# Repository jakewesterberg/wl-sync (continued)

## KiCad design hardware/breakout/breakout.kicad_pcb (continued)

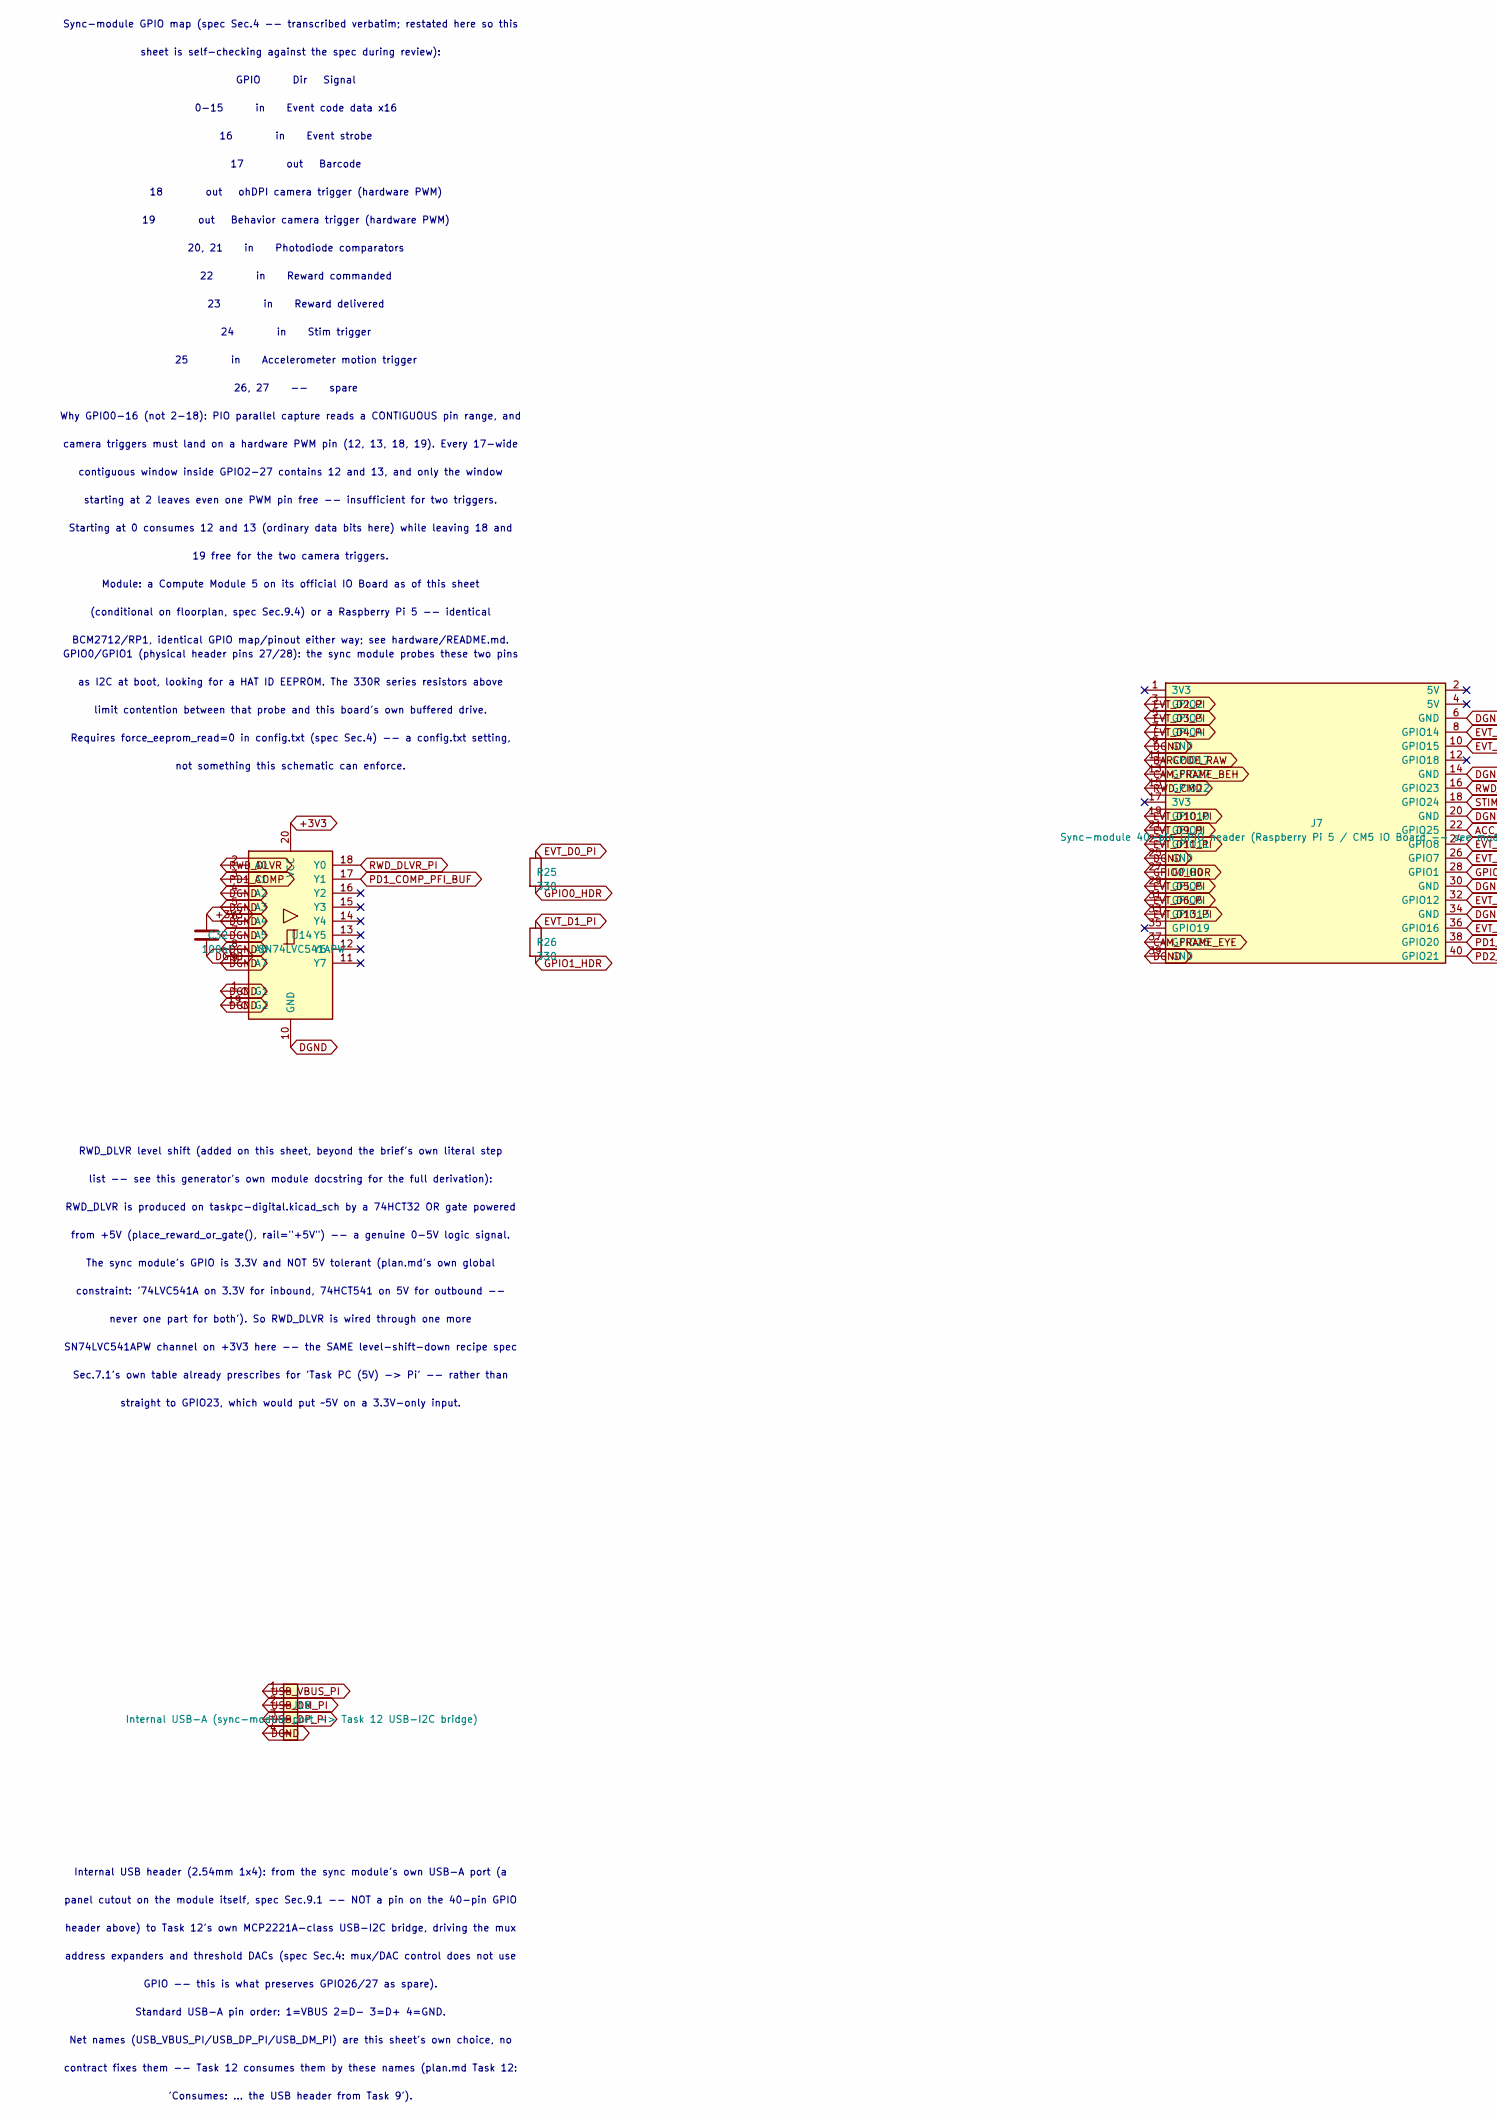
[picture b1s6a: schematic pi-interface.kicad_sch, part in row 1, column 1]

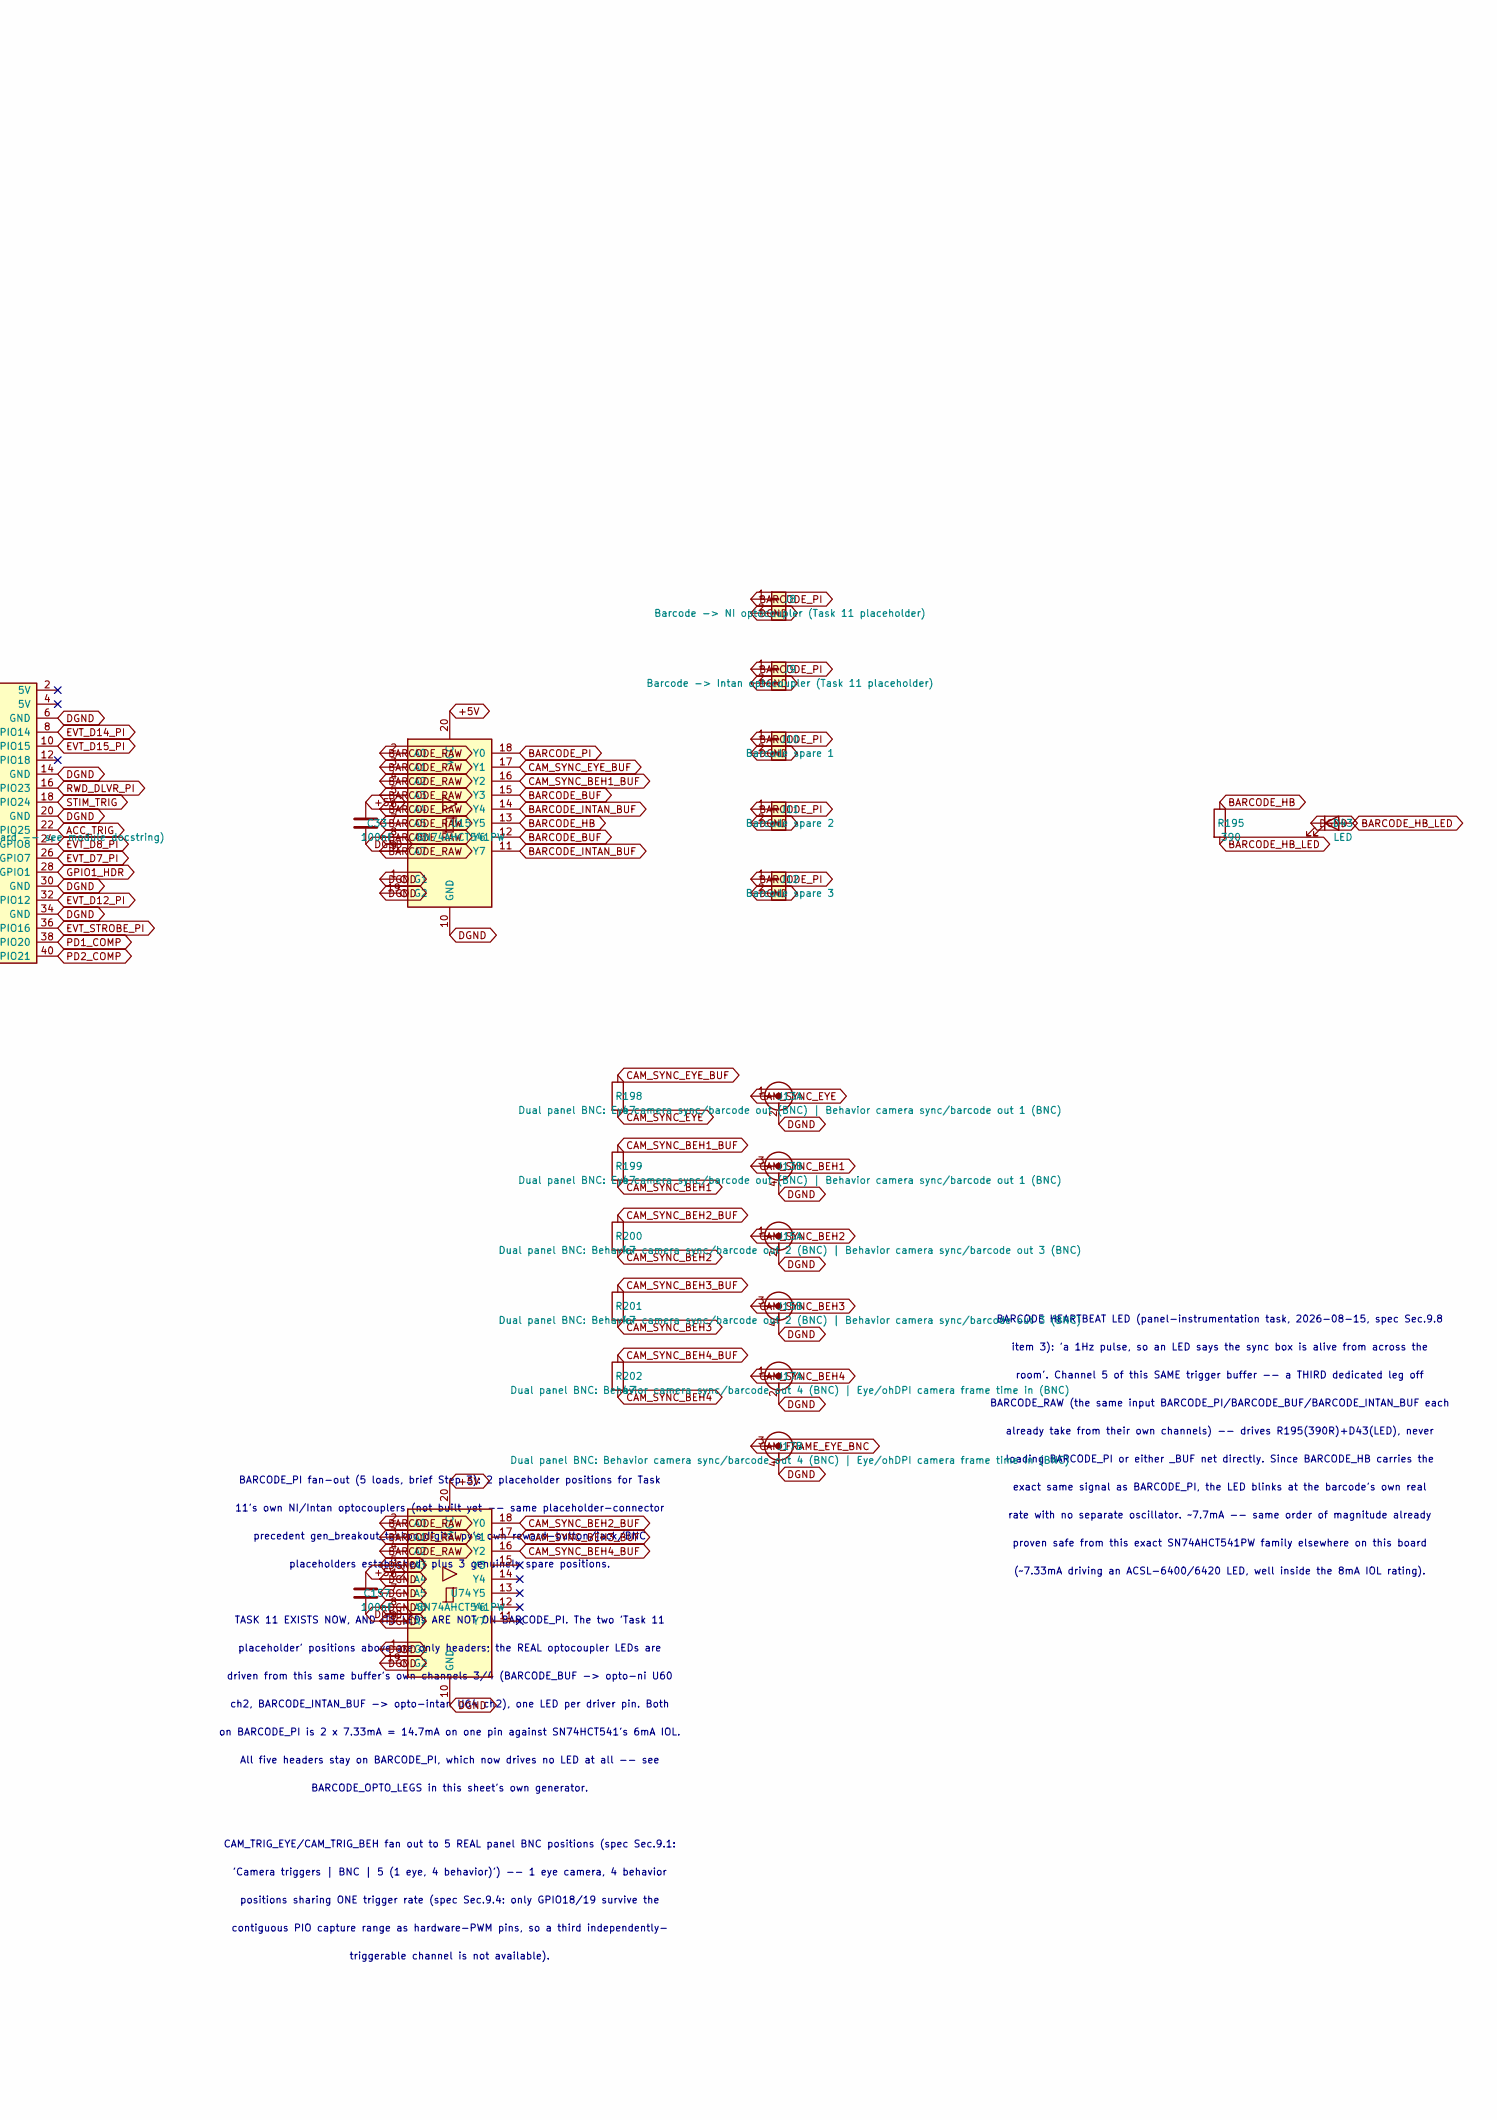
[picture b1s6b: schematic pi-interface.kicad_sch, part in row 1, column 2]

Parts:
C32, C33, C157: 100nF; C_0603_1608Metric
D43: LED; LED_0603_1608Metric_Pad1.05x0.95mm_HandSolder
J7: Sync-module 40-pin GPIO header (Raspberry Pi 5 / 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; PinHeader_2x20_P2.54mm_Vertical
J8: Barcode -> NI optocoupler (Task 11 placeholder); PinHeader_1x02_P2.54mm_Vertical
J9: Barcode -> Intan optocoupler (Task 11 placeholder); PinHeader_1x02_P2.54mm_Vertical
J10: Barcode spare 1; PinHeader_1x02_P2.54mm_Vertical
J11: Barcode spare 2; PinHeader_1x02_P2.54mm_Vertical
J12: Barcode spare 3; PinHeader_1x02_P2.54mm_Vertical
J13: Dual panel BNC: Eye camera sync/barcode out (BNC)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; BNC_Dual_RA_Isolated
J15, J17: Dual panel BNC: Behavior camera sync/barcode out 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; BNC_Dual_RA_Isolated
J18: Internal USB-A (sync-module port -> Task 12 USB-I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; PinHeader_1x04_P2.54mm_Vertical
R25, R26: 330; R_0603_1608Metric
R195: 390; R_0603_1608Metric
R198, R199, R200, R201, R202: 47; R_0603_1608Metric
U14: SN74LVC541APW; Texas_PW0020A_TSSOP-20_4.4x6.5mm_P0.65mm
U15, U74: SN74AHCT541PW; Texas_PW0020A_TSSOP-20_4.4x6.5mm_P0.65mm

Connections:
+3V3: C32.1, U14.20 (VCC); also elsewhere on the board
ACC_TRIG: J7.22 (GPIO25); also elsewhere on the board
BARCODE_BUF: U15.12 (Y6), U15.15 (Y3); also elsewhere on the board
BARCODE_HB: R195.1, U15.13 (Y5)
BARCODE_HB_LED: D43.2 (A), R195.2
BARCODE_INTAN_BUF: U15.11 (Y7), U15.14 (Y4); also elsewhere on the board
BARCODE_PI: J8.1, J9.1, J10.1, J11.1, J12.1, U15.18 (Y0)
BARCODE_RAW: J7.11 (GPIO17), U15.2 (A0), U15.3 (A1), U15.4 (A2), U15.5 (A3), U15.6 (A4), U15.7 (A5), U15.8 (A6), U15.9 (A7), U74.2 (A0), U74.3 (A1), U74.4 (A2)
CAM_FRAME_BEH: J7.13 (GPIO27); also elsewhere on the board
CAM_FRAME_EYE: J7.37 (GPIO26); also elsewhere on the board
CAM_FRAME_EYE_BNC: J17.3 (B_In); also elsewhere on the board
CAM_SYNC_BEH1: J13.3 (B_In), R199.2
CAM_SYNC_BEH1_BUF: R199.1, U15.16 (Y2)
CAM_SYNC_BEH2: J15.1 (A_In), R200.2
CAM_SYNC_BEH2_BUF: R200.1, U74.18 (Y0)
CAM_SYNC_BEH3: J15.3 (B_In), R201.2
CAM_SYNC_BEH3_BUF: R201.1, U74.17 (Y1)
CAM_SYNC_BEH4: J17.1 (A_In), R202.2
CAM_SYNC_BEH4_BUF: R202.1, U74.16 (Y2)
CAM_SYNC_EYE: J13.1 (A_In), R198.2
CAM_SYNC_EYE_BUF: R198.1, U15.17 (Y1)
EVT_D0_PI: R25.1; also elsewhere on the board
EVT_D1_PI: R26.1; also elsewhere on the board
EVT_D2_PI: J7.3 (GPIO2); also elsewhere on the board
EVT_D3_PI: J7.5 (GPIO3); also elsewhere on the board
EVT_D4_PI: J7.7 (GPIO4); also elsewhere on the board
EVT_D5_PI: J7.29 (GPIO5); also elsewhere on the board
EVT_D6_PI: J7.31 (GPIO6); also elsewhere on the board
EVT_D7_PI: J7.26 (GPIO7); also elsewhere on the board
EVT_D8_PI: J7.24 (GPIO8); also elsewhere on the board
EVT_D9_PI: J7.21 (GPIO9); also elsewhere on the board
EVT_D10_PI: J7.19 (GPIO10); also elsewhere on the board
EVT_D11_PI: J7.23 (GPIO11); also elsewhere on the board
EVT_D12_PI: J7.32 (GPIO12); also elsewhere on the board
EVT_D13_PI: J7.33 (GPIO13); also elsewhere on the board
EVT_D14_PI: J7.8 (GPIO14); also elsewhere on the board
EVT_D15_PI: J7.10 (GPIO15); also elsewhere on the board
EVT_STROBE_PI: J7.36 (GPIO16); also elsewhere on the board
GPIO0_HDR: J7.27 (GPIO0), R25.2
GPIO1_HDR: J7.28 (GPIO1), R26.2
PD1_COMP: J7.38 (GPIO20), U14.3 (A1); also elsewhere on the board
PD1_COMP_PFI_BUF: U14.17 (Y1); also elsewhere on the board
PD2_COMP: J7.40 (GPIO21); also elsewhere on the board
RWD_CMD: J7.15 (GPIO22); also elsewhere on the board
RWD_DLVR: U14.2 (A0); also elsewhere on the board
RWD_DLVR_PI: J7.16 (GPIO23), U14.18 (Y0)
STIM_TRIG: J7.18 (GPIO24); also elsewhere on the board
USB_DM_PI: J18.2; also elsewhere on the board
USB_DP_PI: J18.3; also elsewhere on the board
USB_VBUS_PI: J18.1

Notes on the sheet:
not something this schematic can enforce.
Sec.7.1's own table already prescribes for 'Task PC (5V) -> Pi' -- rather than
as I2C at boot, looking for a HAT ID EEPROM. The 330R series resistors above
constraint: '74LVC541A on 3.3V for inbound, 74HCT541 on 5V for outbound --
contiguous window inside GPIO2-27 contains 12 and 13, and only the window
24 in Stim trigger
Sync-module GPIO map (spec Sec.4 -- transcribed verbatim; restated here so this
RWD_DLVR is produced on taskpc-digital.kicad_sch by a 74HCT32 OR gate powered
GPIO0/GPIO1 (physical header pins 27/28): the sync module probes these two pins
ch2, BARCODE_INTAN_BUF -> opto-intan U64 ch2), one LED per driver pin. Both
(~7.33mA driving an ACSL-6400/6420 LED, well inside the 8mA IOL rating).
precedent gen_breakout_taskpc_digital.py's own reward-button/jack/BNC
0-15 in Event code data x16
already take from their own channels) -- drives R195(390R)+D43(LED), never
GPIO Dir Signal
BARCODE HEARTBEAT LED (panel-instrumentation task, 2026-08-15, spec Sec.9.8
SN74LVC541APW channel on +3V3 here -- the SAME level-shift-down recipe spec
exact same signal as BARCODE_PI, the LED blinks at the barcode's own real
camera triggers must land on a hardware PWM pin (12, 13, 18, 19). Every 17-wide
contiguous PIO capture range as hardware-PWM pins, so a third independently-
BCM2712/RP1, identical GPIO map/pinout either way; see hardware/README.md.
CAM_TRIG_EYE/CAM_TRIG_BEH fan out to 5 REAL panel BNC positions (spec Sec.9.1:
placeholders established) plus 3 genuinely spare positions.
Requires force_eeprom_read=0 in config.txt (spec Sec.4) -- a config.txt setting,
23 in Reward delivered
Why GPIO0-16 (not 2-18): PIO parallel capture reads a CONTIGUOUS pin range, and
address expanders and threshold DACs (spec Sec.4: mux/DAC control does not use
11's own NI/Intan optocouplers (not built yet -- same placeholder-connector
never one part for both'). So RWD_DLVR is wired through one more
Net names (USB_VBUS_PI/USB_DP_PI/USB_DM_PI) are this sheet's own choice, no
Standard USB-A pin order: 1=VBUS 2=D- 3=D+ 4=GND.
'Camera triggers | BNC | 5 (1 eye, 4 behavior)') -- 1 eye camera, 4 behavior
BARCODE_RAW (the same input BARCODE_PI/BARCODE_BUF/BARCODE_INTAN_BUF each
on BARCODE_PI is 2 x 7.33mA = 14.7mA on one pin against SN74HCT541's 6mA IOL.
room'. Channel 5 of this SAME trigger buffer -- a THIRD dedicated leg off
panel cutout on the module itself, spec Sec.9.1 -- NOT a pin on the 40-pin GPIO
BARCODE_OPTO_LEGS in this sheet's own generator.
triggerable channel is not available).
16 in Event strobe
18 out ohDPI camera trigger (hardware PWM)

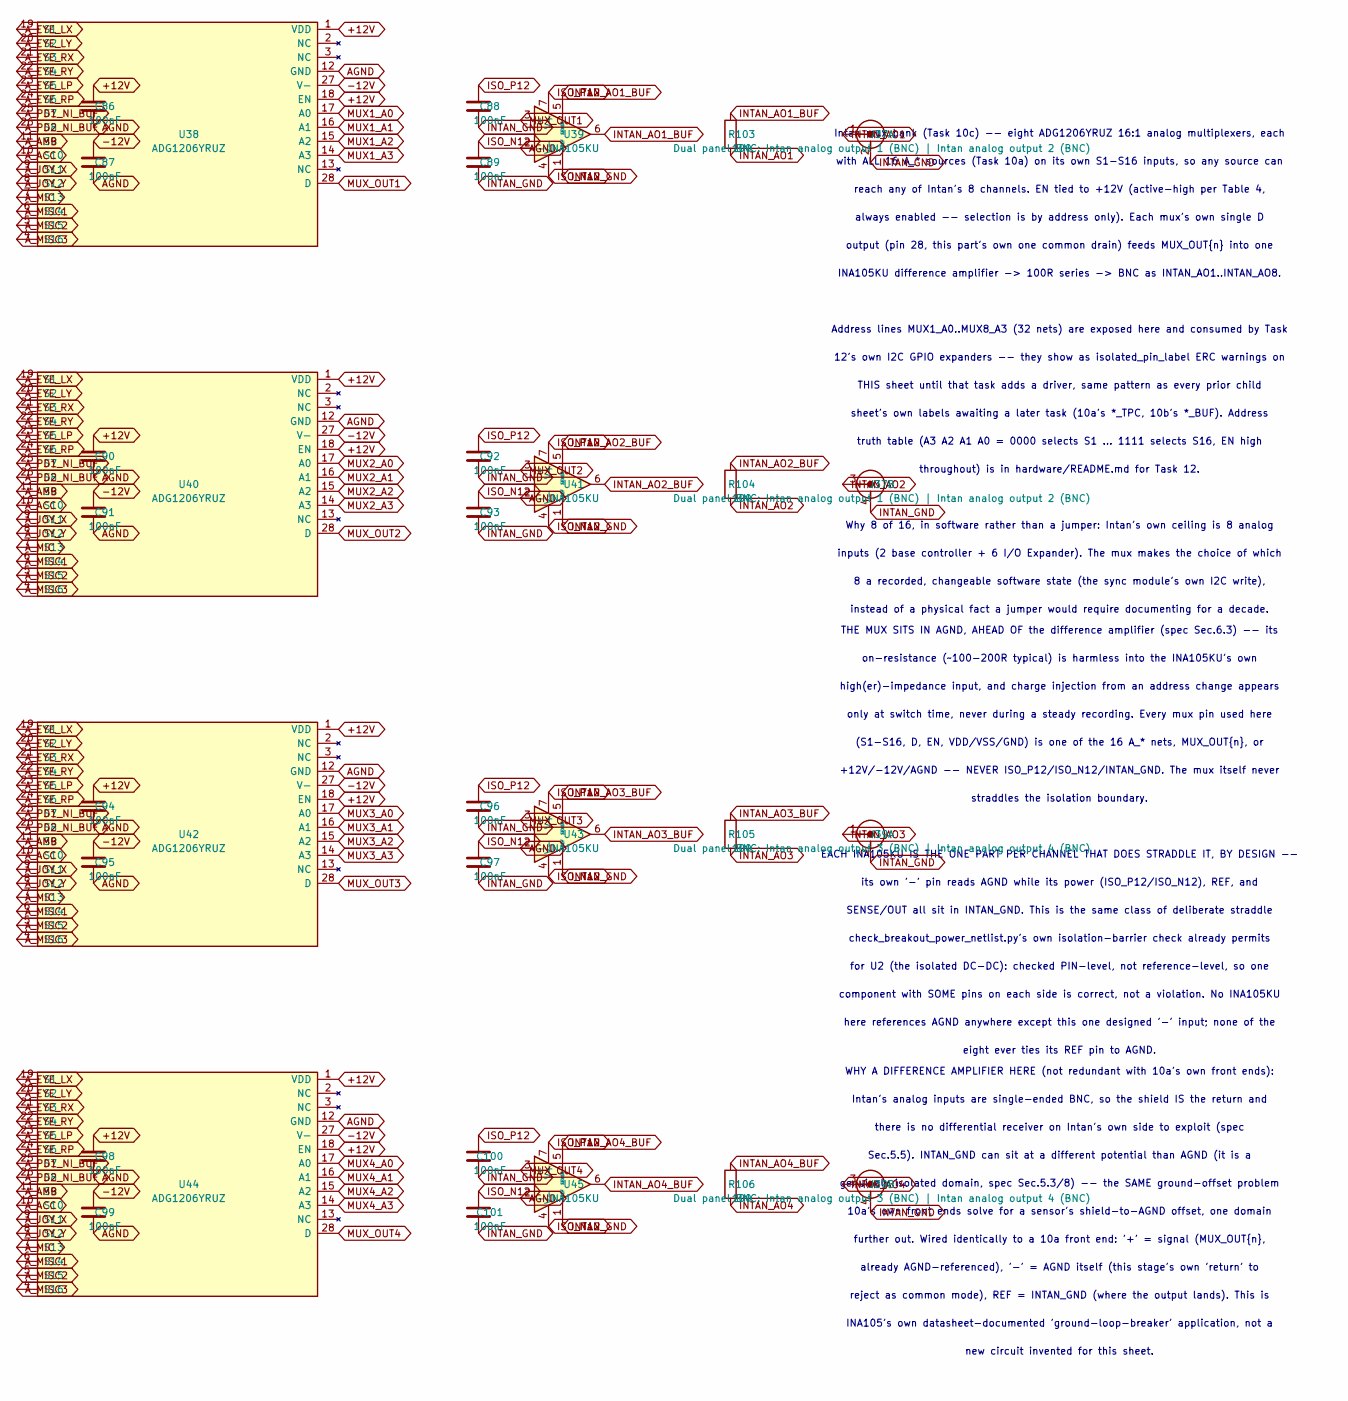
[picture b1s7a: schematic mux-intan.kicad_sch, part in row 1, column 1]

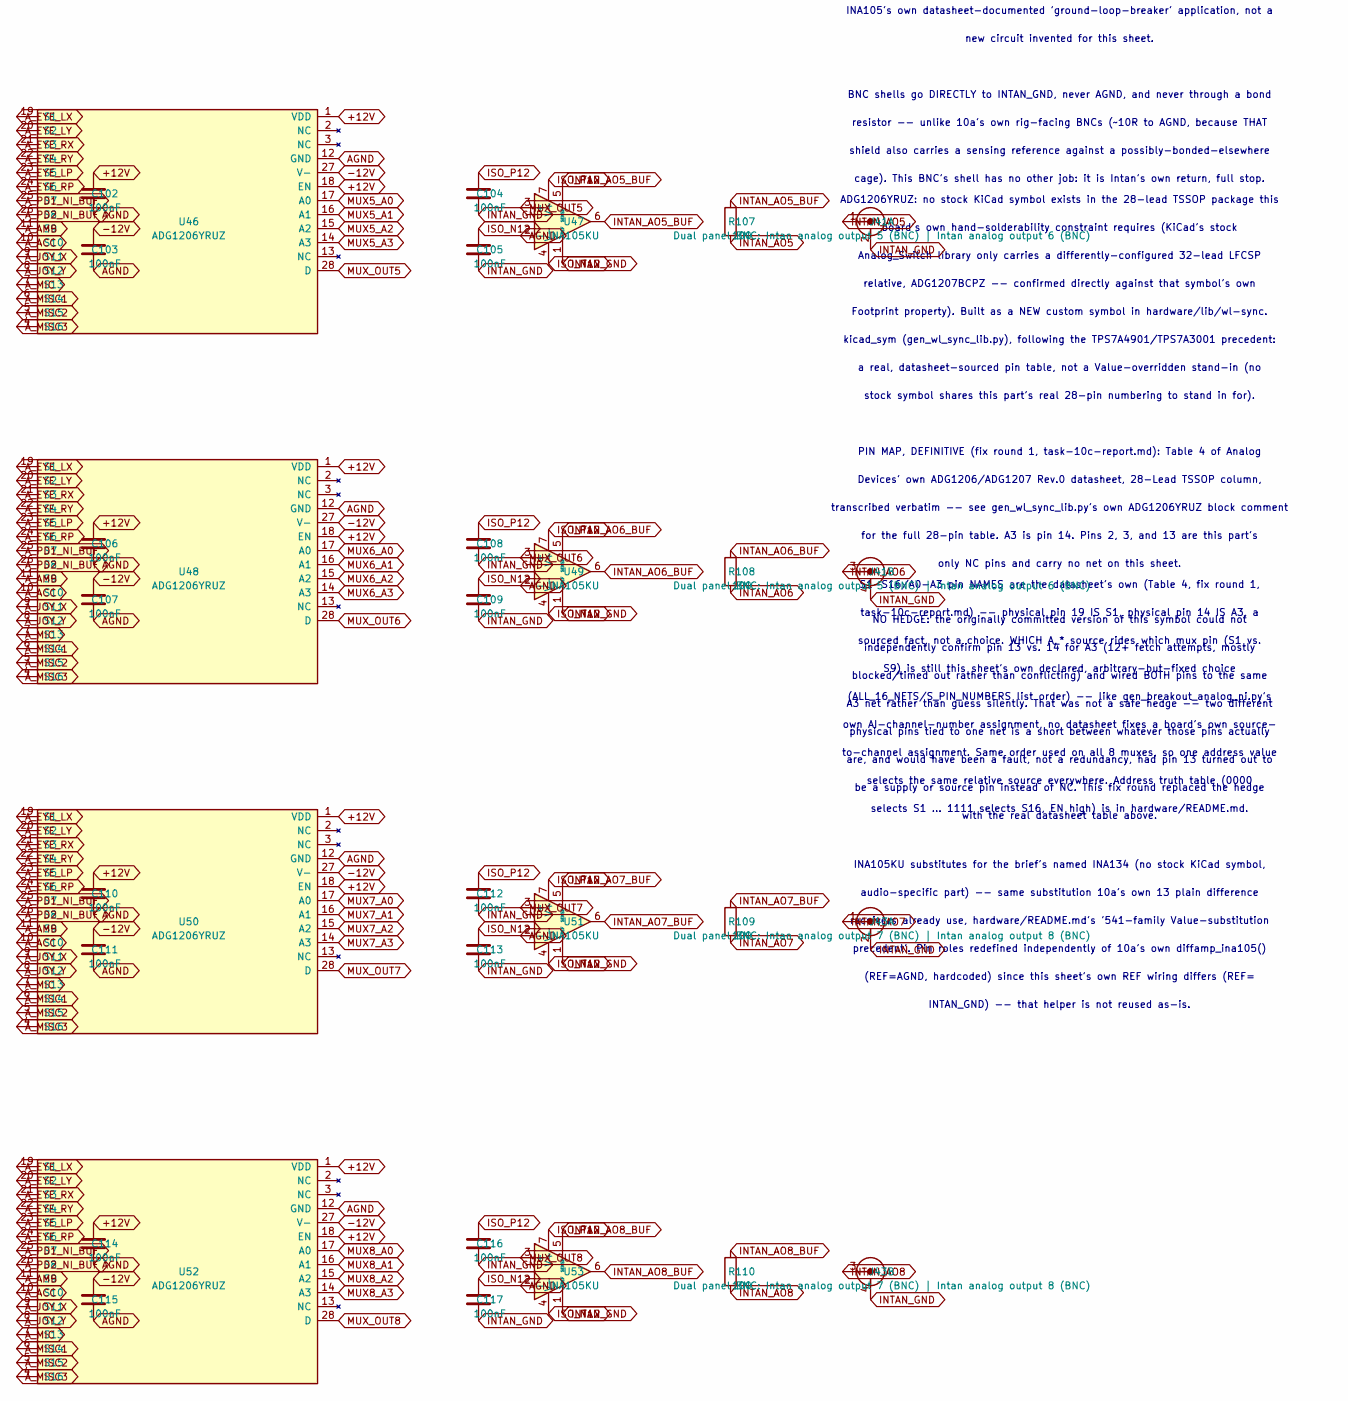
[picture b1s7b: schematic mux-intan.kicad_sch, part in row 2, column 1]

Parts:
C86, C87, C88, C89, C90, C91, C92, C93, C94, C95, C96, C97, C98, C99, C100, C101, C102, C103, C104, C105, C106, C107, C108, C109, C110, C111, C112, C113, C114, C115, C116, C117: 100nF; C_0603_1608Metric
J37: Dual panel BNC: Intan analog output 1 (BNC) | Int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; BNC_Dual_RA_Isolated
J39: Dual panel BNC: Intan analog output 3 (BNC) | Int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; BNC_Dual_RA_Isolated
J41: Dual panel BNC: Intan analog output 5 (BNC) | Int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; BNC_Dual_RA_Isolated
J43: Dual panel BNC: Intan analog output 7 (BNC) | Int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; BNC_Dual_RA_Isolated
R103, R104, R105, R106, R107, R108, R109, R110: 100; R_0603_1608Metric
U38, U40, U42, U44, U46, U48, U50, U52: ADG1206YRUZ; TSSOP-28_4.4x9.7mm_P0.65mm
U39, U41, U43, U45, U47, U49, U51, U53: INA105KU; SOIC-8_3.9x4.9mm_P1.27mm

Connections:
A_ACC: U38.10 (S10), U40.10 (S10), U42.10 (S10), U44.10 (S10), U46.10 (S10), U48.10 (S10), U50.10 (S10), U52.10 (S10); also elsewhere on the board
A_AMB: U38.11 (S9), U40.11 (S9), U42.11 (S9), U44.11 (S9), U46.11 (S9), U48.11 (S9), U50.11 (S9), U52.11 (S9); also elsewhere on the board
A_EYE_LP: U38.23 (S5), U40.23 (S5), U42.23 (S5), U44.23 (S5), U46.23 (S5), U48.23 (S5), U50.23 (S5), U52.23 (S5); also elsewhere on the board
A_EYE_LX: U38.19 (S1), U40.19 (S1), U42.19 (S1), U44.19 (S1), U46.19 (S1), U48.19 (S1), U50.19 (S1), U52.19 (S1); also elsewhere on the board
A_EYE_LY: U38.20 (S2), U40.20 (S2), U42.20 (S2), U44.20 (S2), U46.20 (S2), U48.20 (S2), U50.20 (S2), U52.20 (S2); also elsewhere on the board
A_EYE_RP: U38.24 (S6), U40.24 (S6), U42.24 (S6), U44.24 (S6), U46.24 (S6), U48.24 (S6), U50.24 (S6), U52.24 (S6); also elsewhere on the board
A_EYE_RX: U38.21 (S3), U40.21 (S3), U42.21 (S3), U44.21 (S3), U46.21 (S3), U48.21 (S3), U50.21 (S3), U52.21 (S3); also elsewhere on the board
A_EYE_RY: U38.22 (S4), U40.22 (S4), U42.22 (S4), U44.22 (S4), U46.22 (S4), U48.22 (S4), U50.22 (S4), U52.22 (S4); also elsewhere on the board
A_JOY_X: U38.9 (S11), U40.9 (S11), U42.9 (S11), U44.9 (S11), U46.9 (S11), U48.9 (S11), U50.9 (S11), U52.9 (S11); also elsewhere on the board
A_JOY_Y: U38.8 (S12), U40.8 (S12), U42.8 (S12), U44.8 (S12), U46.8 (S12), U48.8 (S12), U50.8 (S12), U52.8 (S12); also elsewhere on the board
A_MIC: U38.7 (S13), U40.7 (S13), U42.7 (S13), U44.7 (S13), U46.7 (S13), U48.7 (S13), U50.7 (S13), U52.7 (S13); also elsewhere on the board
A_MISC1: U38.6 (S14), U40.6 (S14), U42.6 (S14), U44.6 (S14), U46.6 (S14), U48.6 (S14), U50.6 (S14), U52.6 (S14); also elsewhere on the board
A_MISC2: U38.5 (S15), U40.5 (S15), U42.5 (S15), U44.5 (S15), U46.5 (S15), U48.5 (S15), U50.5 (S15), U52.5 (S15); also elsewhere on the board
A_MISC3: U38.4 (S16), U40.4 (S16), U42.4 (S16), U44.4 (S16), U46.4 (S16), U48.4 (S16), U50.4 (S16), U52.4 (S16); also elsewhere on the board
A_PD1_NI_BUF: U38.25 (S7), U40.25 (S7), U42.25 (S7), U44.25 (S7), U46.25 (S7), U48.25 (S7), U50.25 (S7), U52.25 (S7); also elsewhere on the board
A_PD2_NI_BUF: U38.26 (S8), U40.26 (S8), U42.26 (S8), U44.26 (S8), U46.26 (S8), U48.26 (S8), U50.26 (S8), U52.26 (S8); also elsewhere on the board
INTAN_AO1: J37.1 (A_In), R103.2
INTAN_AO1_BUF: R103.1, U39.5 (SENSE), U39.6
INTAN_AO2: J37.3 (B_In), R104.2
INTAN_AO2_BUF: R104.1, U41.5 (SENSE), U41.6
INTAN_AO3: J39.1 (A_In), R105.2
INTAN_AO3_BUF: R105.1, U43.5 (SENSE), U43.6
INTAN_AO4: J39.3 (B_In), R106.2
INTAN_AO4_BUF: R106.1, U45.5 (SENSE), U45.6
INTAN_AO5: J41.1 (A_In), R107.2
INTAN_AO5_BUF: R107.1, U47.5 (SENSE), U47.6
INTAN_AO6: J41.3 (B_In), R108.2
INTAN_AO6_BUF: R108.1, U49.5 (SENSE), U49.6
INTAN_AO7: J43.1 (A_In), R109.2
INTAN_AO7_BUF: R109.1, U51.5 (SENSE), U51.6
INTAN_AO8: J43.3 (B_In), R110.2
INTAN_AO8_BUF: R110.1, U53.5 (SENSE), U53.6
INTAN_GND: C88.2, C89.2, C92.2, C93.2, C96.2, C97.2, C100.2, C101.2, C104.2, C105.2, C108.2, C109.2, C112.2, C113.2, C116.2, C117.2, J37.2 (A_Ext), J37.4 (B_Ext), J39.2 (A_Ext), J39.4 (B_Ext), J41.2 (A_Ext), J41.4 (B_Ext), J43.2 (A_Ext), J43.4 (B_Ext), U39.1 (REF), U41.1 (REF), U43.1 (REF), U45.1 (REF), U47.1 (REF), U49.1 (REF), U51.1 (REF), U53.1 (REF); also elsewhere on the board
ISO_N12: C89.1, C93.1, C97.1, C101.1, C105.1, C109.1, C113.1, C117.1, U39.4 (V-), U41.4 (V-), U43.4 (V-), U45.4 (V-), U47.4 (V-), U49.4 (V-), U51.4 (V-), U53.4 (V-); also elsewhere on the board
ISO_P12: C88.1, C92.1, C96.1, C100.1, C104.1, C108.1, C112.1, C116.1, U39.7 (V+), U41.7 (V+), U43.7 (V+), U45.7 (V+), U47.7 (V+), U49.7 (V+), U51.7 (V+), U53.7 (V+); also elsewhere on the board
MUX1_A0: U38.17 (A0); also elsewhere on the board
MUX1_A1: U38.16 (A1); also elsewhere on the board
MUX1_A2: U38.15 (A2); also elsewhere on the board
MUX1_A3: U38.14 (A3); also elsewhere on the board
MUX2_A0: U40.17 (A0); also elsewhere on the board
MUX2_A1: U40.16 (A1); also elsewhere on the board
MUX2_A2: U40.15 (A2); also elsewhere on the board
MUX2_A3: U40.14 (A3); also elsewhere on the board
MUX3_A0: U42.17 (A0); also elsewhere on the board
MUX3_A1: U42.16 (A1); also elsewhere on the board
MUX3_A2: U42.15 (A2); also elsewhere on the board
MUX3_A3: U42.14 (A3); also elsewhere on the board
MUX4_A0: U44.17 (A0); also elsewhere on the board
MUX4_A1: U44.16 (A1); also elsewhere on the board
MUX4_A2: U44.15 (A2); also elsewhere on the board
MUX4_A3: U44.14 (A3); also elsewhere on the board
MUX5_A0: U46.17 (A0); also elsewhere on the board
MUX5_A1: U46.16 (A1); also elsewhere on the board
MUX5_A2: U46.15 (A2); also elsewhere on the board
MUX5_A3: U46.14 (A3); also elsewhere on the board
MUX6_A0: U48.17 (A0); also elsewhere on the board
MUX6_A1: U48.16 (A1); also elsewhere on the board
MUX6_A2: U48.15 (A2); also elsewhere on the board
MUX6_A3: U48.14 (A3); also elsewhere on the board
MUX7_A0: U50.17 (A0); also elsewhere on the board
MUX7_A1: U50.16 (A1); also elsewhere on the board
MUX7_A2: U50.15 (A2); also elsewhere on the board
MUX7_A3: U50.14 (A3); also elsewhere on the board
MUX8_A0: U52.17 (A0); also elsewhere on the board
MUX8_A1: U52.16 (A1); also elsewhere on the board
MUX8_A2: U52.15 (A2); also elsewhere on the board
MUX8_A3: U52.14 (A3); also elsewhere on the board
MUX_OUT1: U38.28 (D), U39.3 (+)
MUX_OUT2: U40.28 (D), U41.3 (+)
MUX_OUT3: U42.28 (D), U43.3 (+)
MUX_OUT4: U44.28 (D), U45.3 (+)
MUX_OUT5: U46.28 (D), U47.3 (+)
MUX_OUT6: U48.28 (D), U49.3 (+)
MUX_OUT7: U50.28 (D), U51.3 (+)
MUX_OUT8: U52.28 (D), U53.3 (+)

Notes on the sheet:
Intan mux bank (Task 10c) -- eight ADG1206YRUZ 16:1 analog multiplexers, each
with ALL 16 A_* sources (Task 10a) on its own S1-S16 inputs, so any source can
reach any of Intan's 8 channels. EN tied to +12V (active-high per Table 4,
always enabled -- selection is by address only). Each mux's own single D
output (pin 28, this part's own one common drain) feeds MUX_OUT{n} into one
INA105KU difference amplifier -> 100R series -> BNC as INTAN_AO1..INTAN_AO8.
Address lines MUX1_A0..MUX8_A3 (32 nets) are exposed here and consumed by Task
12's own I2C GPIO expanders -- they show as isolated_pin_label ERC warnings on
THIS sheet until that task adds a driver, same pattern as every prior child
sheet's own labels awaiting a later task (10a's *_TPC, 10b's *_BUF). Address
truth table (A3 A2 A1 A0 = 0000 selects S1 ... 1111 selects S16, EN high
throughout) is in hardware/README.md for Task 12.
Why 8 of 16, in software rather than a jumper: Intan's own ceiling is 8 analog
inputs (2 base controller + 6 I/O Expander). The mux makes the choice of which
8 a recorded, changeable software state (the sync module's own I2C write),
instead of a physical fact a jumper would require documenting for a decade.
THE MUX SITS IN AGND, AHEAD OF the difference amplifier (spec Sec.6.3) -- its
on-resistance (~100-200R typical) is harmless into the INA105KU's own
high(er)-impedance input, and charge injection from an address change appears
only at switch time, never during a steady recording. Every mux pin used here
(S1-S16, D, EN, VDD/VSS/GND) is one of the 16 A_* nets, MUX_OUT{n}, or
+12V/-12V/AGND -- NEVER ISO_P12/ISO_N12/INTAN_GND. The mux itself never
straddles the isolation boundary.
EACH INA105KU IS THE ONE PART PER CHANNEL THAT DOES STRADDLE IT, BY DESIGN --
its own '-' pin reads AGND while its power (ISO_P12/ISO_N12), REF, and
SENSE/OUT all sit in INTAN_GND. This is the same class of deliberate straddle
check_breakout_power_netlist.py's own isolation-barrier check already permits
for U2 (the isolated DC-DC): checked PIN-level, not reference-level, so one
component with SOME pins on each side is correct, not a violation. No INA105KU
here references AGND anywhere except this one designed '-' input; none of the
eight ever ties its REF pin to AGND.
WHY A DIFFERENCE AMPLIFIER HERE (not redundant with 10a's own front ends):
Intan's analog inputs are single-ended BNC, so the shield IS the return and
there is no differential receiver on Intan's own side to exploit (spec
Sec.5.5). INTAN_GND can sit at a different potential than AGND (it is a
genuinely isolated domain, spec Sec.5.3/8) -- the SAME ground-offset problem
10a's own front ends solve for a sensor's shield-to-AGND offset, one domain
further out. Wired identically to a 10a front end: '+' = signal (MUX_OUT{n},
already AGND-referenced), '-' = AGND itself (this stage's own 'return' to
reject as common mode), REF = INTAN_GND (where the output lands). This is
